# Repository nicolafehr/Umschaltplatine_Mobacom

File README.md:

# Umschaltplatine_Mobacom
PCB um die Steuerung einer Testanlage mit verschiedenen Zentralen zu ermöglichen. Zudem können verschiedene Gleisabschnitte angesteuert werden können.

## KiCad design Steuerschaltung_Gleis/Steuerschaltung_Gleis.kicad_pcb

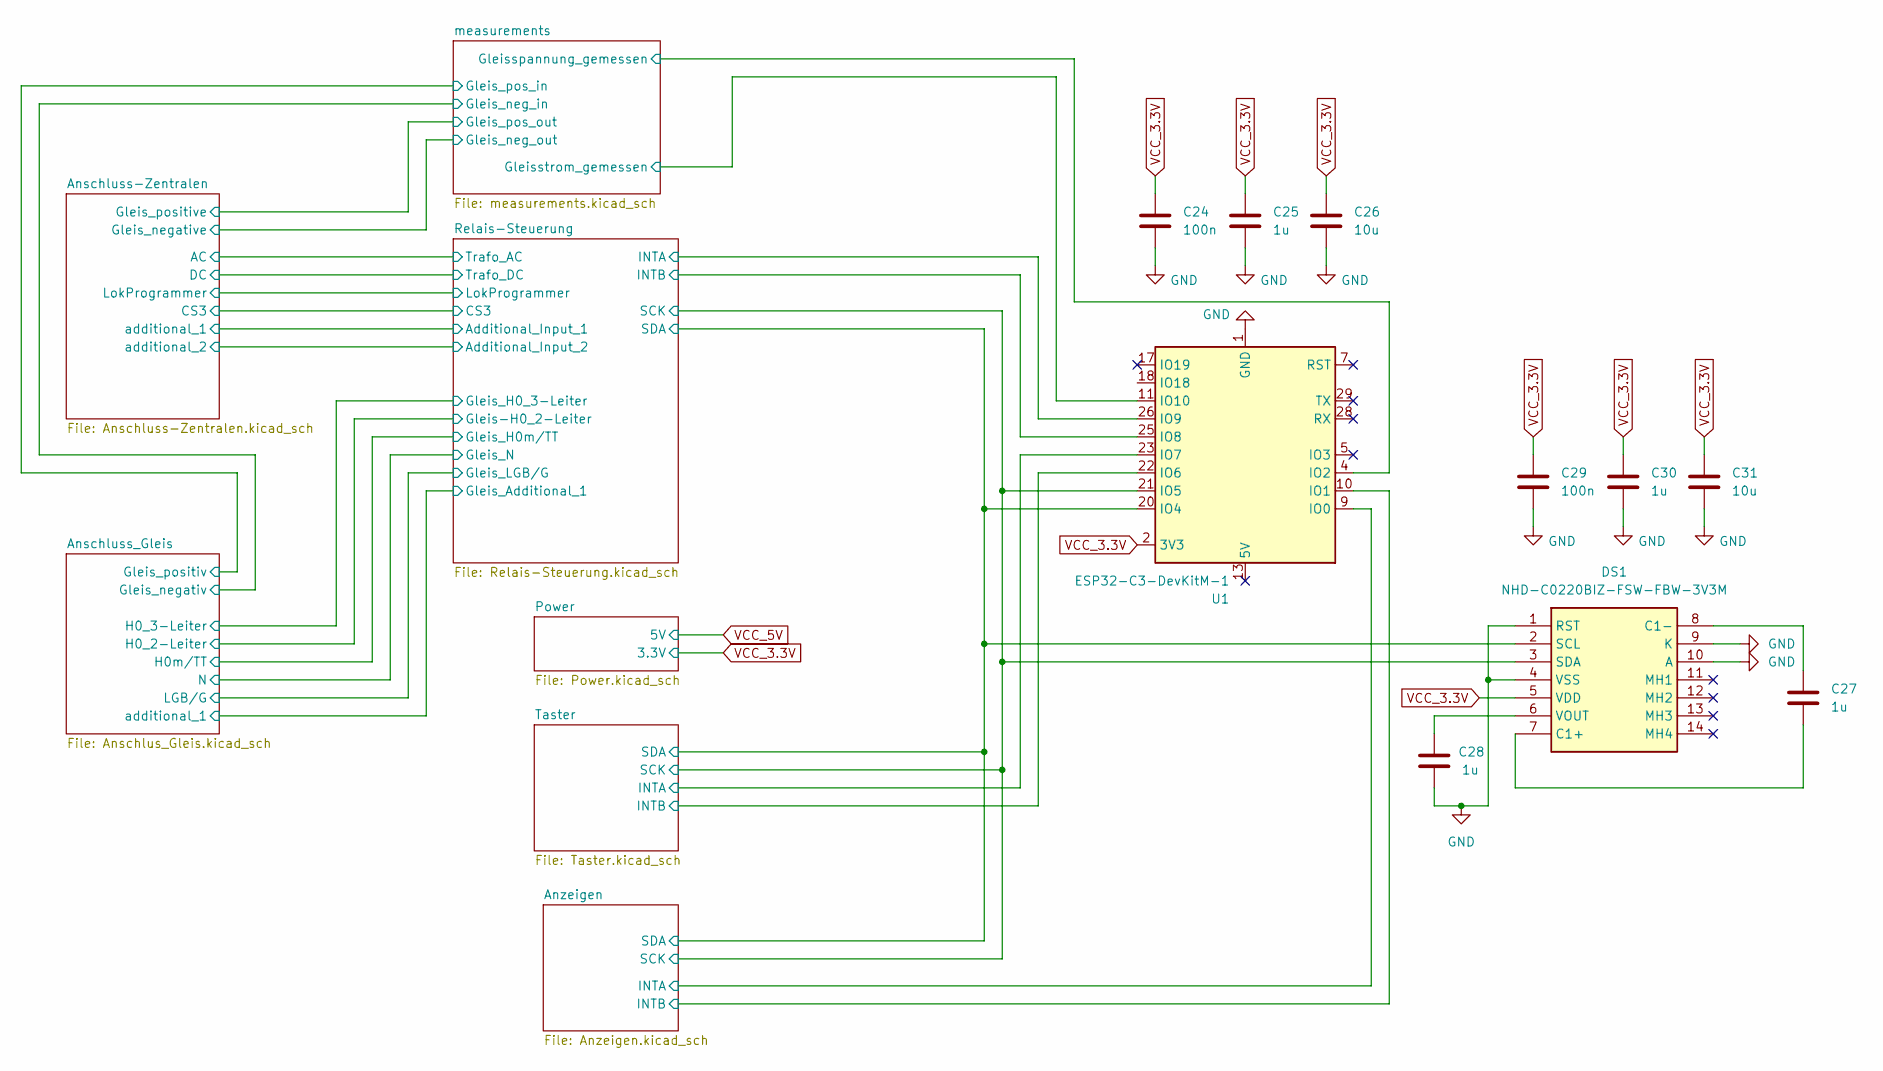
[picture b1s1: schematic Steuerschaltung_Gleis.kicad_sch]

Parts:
C24, C29: 100n; C_0805_2012Metric
C25, C27, C28, C30: 1u; C_0805_2012Metric
C26, C31: 10u; C_0805_2012Metric
DS1: NHD-C0220BIZ-FSW-FBW-3V3M; NHDC0220BIZFSWFBW3V3M; Mouser Part Number 763-C0220BIZ-FSW-FBW
U1: ESP32-C3-DevKitM-1

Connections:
/Anzeigen/INTA: U1.9 (IO0); also elsewhere on the board
/Anzeigen/INTB: U1.10 (IO1); also elsewhere on the board
/Anzeigen/SCK: DS1.3 (SDA), U1.21 (IO5); also elsewhere on the board
/Anzeigen/SDA: DS1.2 (SCL), U1.20 (IO4); also elsewhere on the board
/Relais-Steuerung/INTA: U1.26 (IO9); also elsewhere on the board
/Relais-Steuerung/INTB: U1.25 (IO8); also elsewhere on the board
/Taster/INTA: U1.23 (IO7); also elsewhere on the board
/Taster/INTB: U1.22 (IO6); also elsewhere on the board
/measurements/Gleisspannung_gemessen: U1.4 (IO2); also elsewhere on the board
/measurements/Gleisstrom_gemessen: U1.11 (IO10); also elsewhere on the board
GND: C24.2, C25.2, C26.2, C28.2, C29.2, C30.2, C31.2, DS1.1 (RST), DS1.4 (VSS), DS1.9 (K), DS1.10 (A), U1.1 (GND), U1.6 (GND), U1.8 (GND), U1.12 (GND), U1.15 (GND), U1.16 (GND), U1.19 (GND), U1.24 (GND), U1.27 (GND), U1.30 (GND); also elsewhere on the board
unnamed: C27.2, DS1.7 (C1+)
unnamed: C27.1, DS1.8 (C1-)
unnamed: C28.1, DS1.6 (VOUT)
VCC_3.3V: C24.1, C25.1, C26.1, C29.1, C30.1, C31.1, DS1.5 (VDD), U1.2 (3V3), U1.3 (3V3); also elsewhere on the board

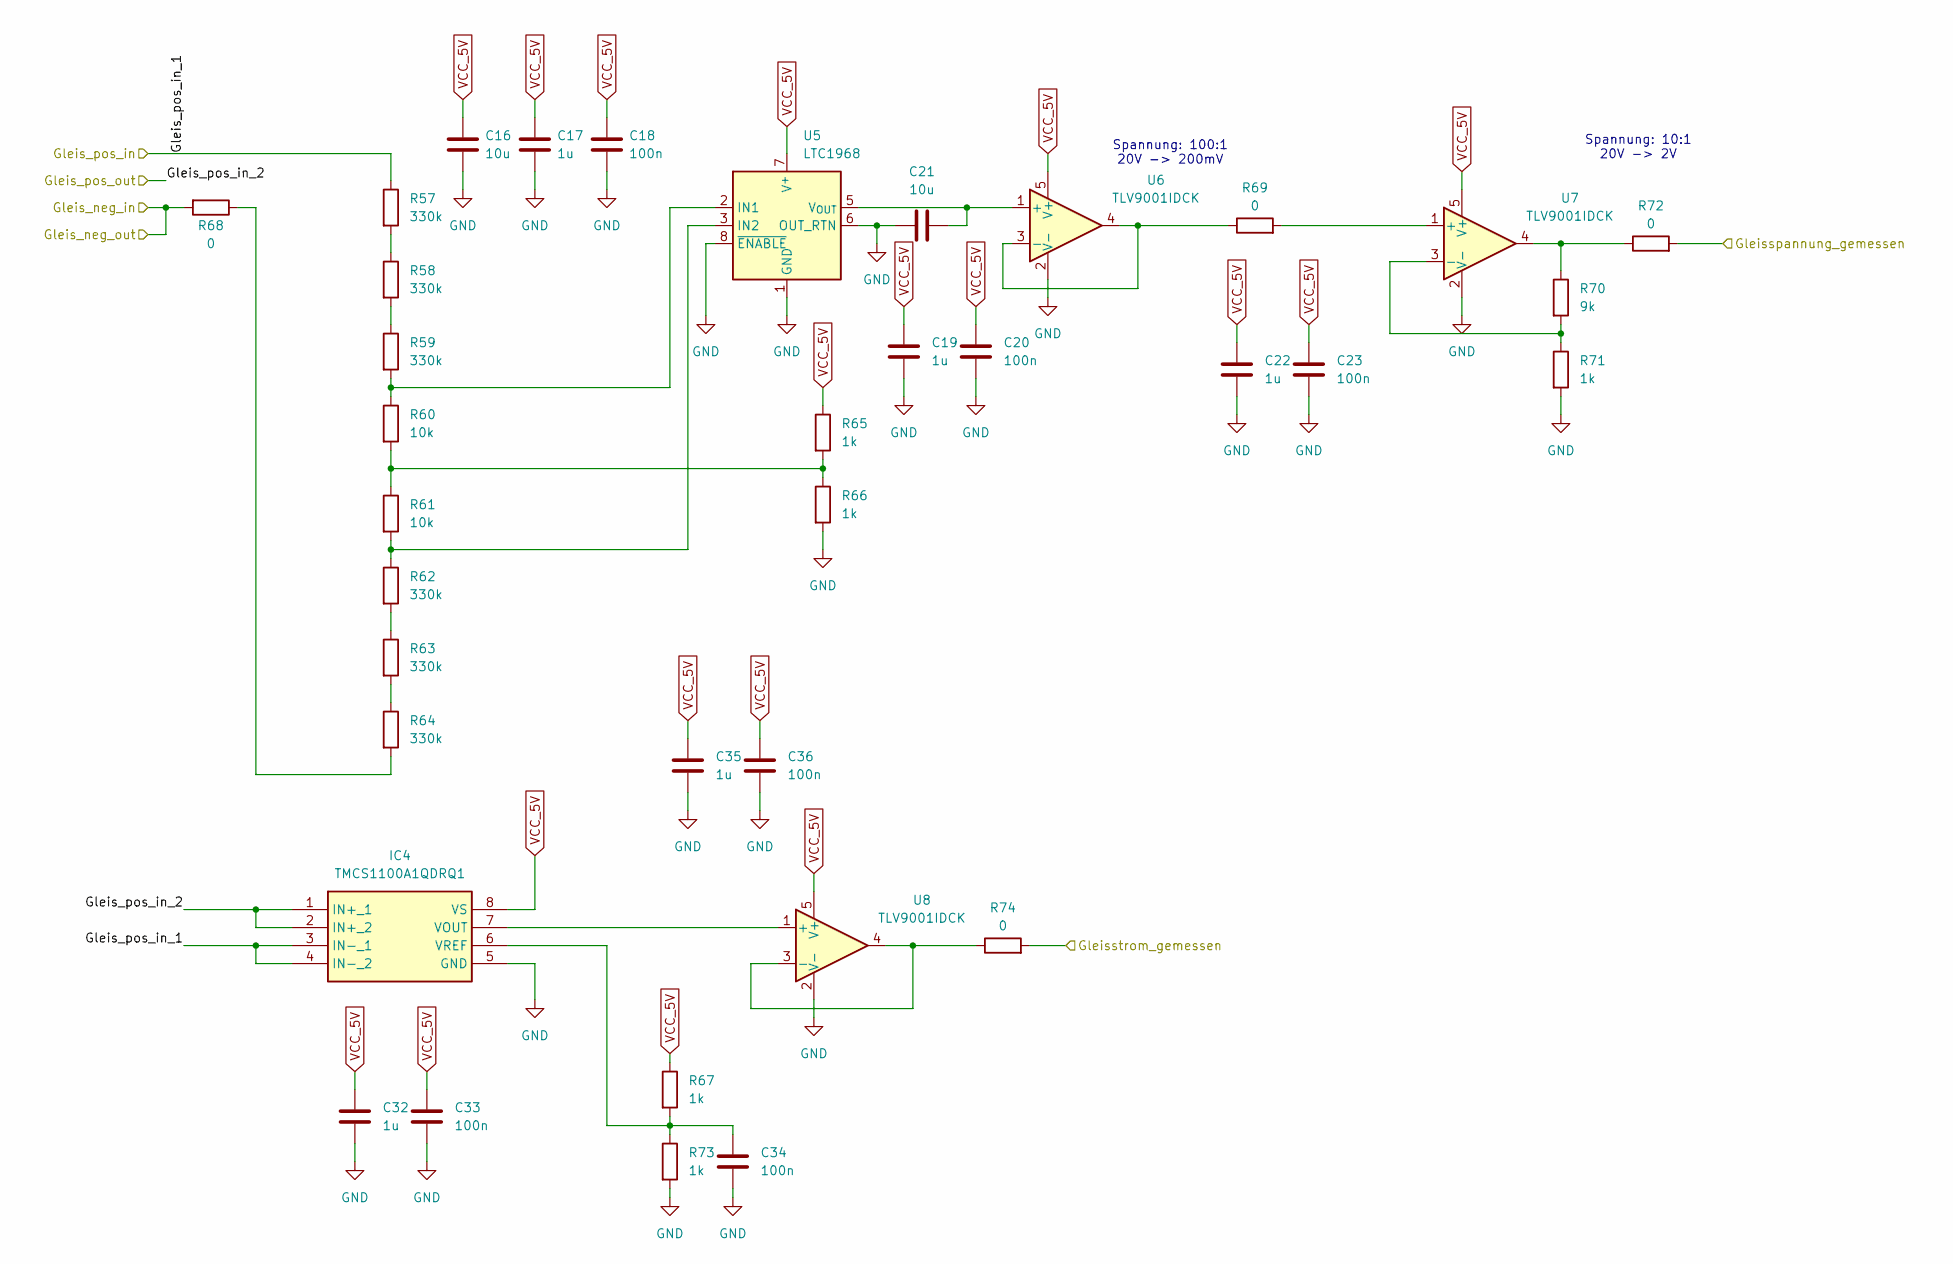
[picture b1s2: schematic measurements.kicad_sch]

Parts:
C16, C21: 10u; C_0805_2012Metric
C17, C19, C22, C32, C35: 1u; C_0805_2012Metric
C18, C20, C23, C33, C34, C36: 100n; C_0805_2012Metric
IC4: TMCS1100A1QDRQ1; SOIC127P600X175-8N; Mouser Part Number 595-TMCS1100A1QDRQ1
R57, R58, R59, R62, R63, R64: 330k; R_0805_2012Metric
R60, R61: 10k; R_0805_2012Metric
R65, R66, R67, R71, R73: 1k; R_0805_2012Metric
R68, R69, R72, R74: 0; R_0805_2012Metric
R70: 9k; R_0805_2012Metric
U5: LTC1968; MSOP-8_3x3mm_P0.65mm
U6, U7, U8: TLV9001IDCK; SOT-353_SC-70-5

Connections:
/Anschluss-Zentralen/Gleis_negative: R68.2; also elsewhere on the board
/measurements/Gleis_pos_in_1: IC4.3 (IN-_1), IC4.4 (IN-_2), R57.1; also elsewhere on the board
/measurements/Gleis_pos_in_2: IC4.1 (IN+_1), IC4.2 (IN+_2); also elsewhere on the board
/measurements/Gleisspannung_gemessen: R72.2; also elsewhere on the board
/measurements/Gleisstrom_gemessen: R74.2; also elsewhere on the board
GND: C16.2, C17.2, C18.2, C19.2, C20.2, C21.1, C22.2, C23.2, C32.2, C33.2, C34.2, C35.2, C36.2, IC4.5 (GND), R66.2, R71.2, R73.2, U5.1 (GND), U5.6 (OUT_RTN), U5.8 (~ENABLE), U6.2 (V-), U7.2 (V-), U8.2 (V-); also elsewhere on the board
unnamed: IC4.7 (VOUT), U8.1 (+)
unnamed: C34.1, IC4.6 (VREF), R67.2, R73.1
unnamed: R57.2, R58.1
unnamed: R58.2, R59.1
unnamed: R60.2, R61.1, R65.2, R66.1
unnamed: R62.2, R63.1
unnamed: R63.2, R64.1
unnamed: R64.2, R68.1
unnamed: R70.1, R72.1, U7.4
unnamed: R59.2, R60.1, U5.2 (IN1)
unnamed: R61.2, R62.1, U5.3 (IN2)
unnamed: C21.2, U5.5 (V_{OUT}), U6.1 (+)
unnamed: R69.1, U6.3 (-), U6.4
unnamed: R69.2, U7.1 (+)
unnamed: R70.2, R71.1, U7.3 (-)
unnamed: R74.1, U8.3 (-), U8.4
VCC_5V: C16.1, C17.1, C18.1, C19.1, C20.1, C22.1, C23.1, C32.1, C33.1, C35.1, C36.1, IC4.8 (VS), R65.1, R67.1, U5.7 (V^{+}), U6.5 (V+), U7.5 (V+), U8.5 (V+); also elsewhere on the board

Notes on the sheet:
Spannung: 100:1 20V -> 200mV
Spannung: 10:1 20V -> 2V

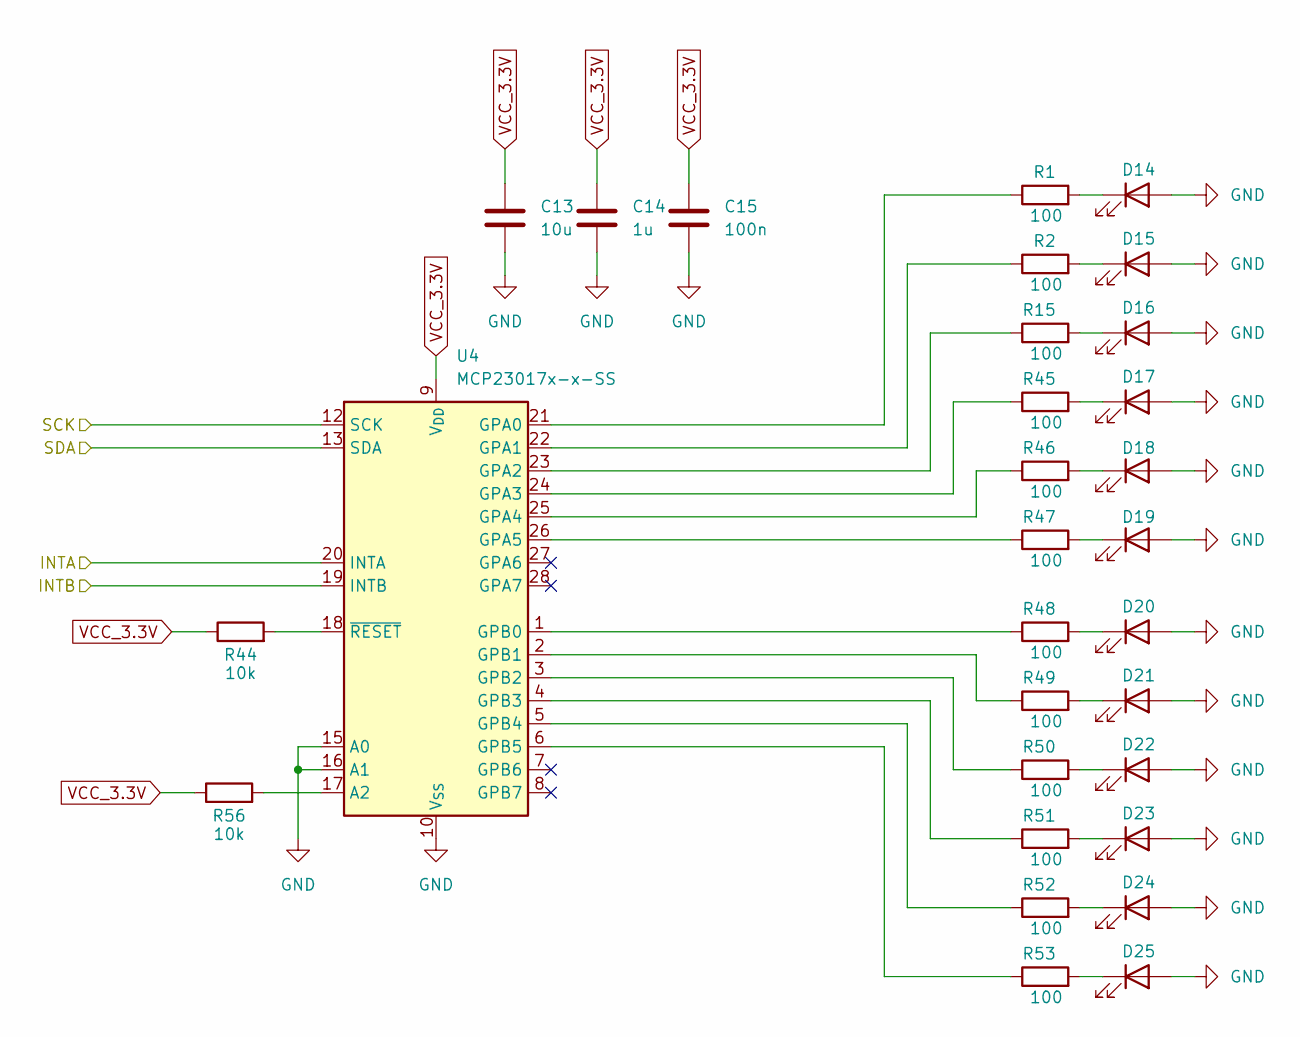
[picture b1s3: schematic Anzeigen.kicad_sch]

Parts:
C13: 10u; C_0805_2012Metric
C14: 1u; C_0805_2012Metric
C15: 100n; C_0805_2012Metric
D14, D15, D16, D17, D18, D19, D20, D21, D22, D23, D24, D25: LED; LED_D3.0mm
R1, R2, R15, R45, R46, R47, R48, R49, R50, R51, R52, R53: 100; R_0805_2012Metric
R44, R56: 10k; R_0805_2012Metric
U4: MCP23017x-x-SS; SSOP-28_5.3x10.2mm_P0.65mm

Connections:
/Anzeigen/INTA: U4.20 (INTA); also elsewhere on the board
/Anzeigen/INTB: U4.19 (INTB); also elsewhere on the board
/Anzeigen/SCK: U4.12 (SCK); also elsewhere on the board
/Anzeigen/SDA: U4.13 (SDA); also elsewhere on the board
GND: C13.2, C14.2, C15.2, D14.2 (A), D15.2 (A), D16.2 (A), D17.2 (A), D18.2 (A), D19.2 (A), D20.2 (A), D21.2 (A), D22.2 (A), D23.2 (A), D24.2 (A), D25.2 (A), U4.10 (V_{SS}), U4.15 (A0), U4.16 (A1); also elsewhere on the board
unnamed: D14.1 (K), R1.2
unnamed: D15.1 (K), R2.2
unnamed: D16.1 (K), R15.2
unnamed: D17.1 (K), R45.2
unnamed: D18.1 (K), R46.2
unnamed: D19.1 (K), R47.2
unnamed: D20.1 (K), R48.2
unnamed: D21.1 (K), R49.2
unnamed: D22.1 (K), R50.2
unnamed: D23.1 (K), R51.2
unnamed: D24.1 (K), R52.2
unnamed: D25.1 (K), R53.2
unnamed: R56.2, U4.17 (A2)
unnamed: R1.1, U4.21 (GPA0)
unnamed: R2.1, U4.22 (GPA1)
unnamed: R15.1, U4.23 (GPA2)
unnamed: R45.1, U4.24 (GPA3)
unnamed: R46.1, U4.25 (GPA4)
unnamed: R47.1, U4.26 (GPA5)
unnamed: R48.1, U4.1 (GPB0)
unnamed: R49.1, U4.2 (GPB1)
unnamed: R50.1, U4.3 (GPB2)
unnamed: R51.1, U4.4 (GPB3)
unnamed: R52.1, U4.5 (GPB4)
unnamed: R53.1, U4.6 (GPB5)
unnamed: R44.2, U4.18 (~RESET)
VCC_3.3V: C13.1, C14.1, C15.1, R44.1, R56.1, U4.9 (V_{DD}); also elsewhere on the board

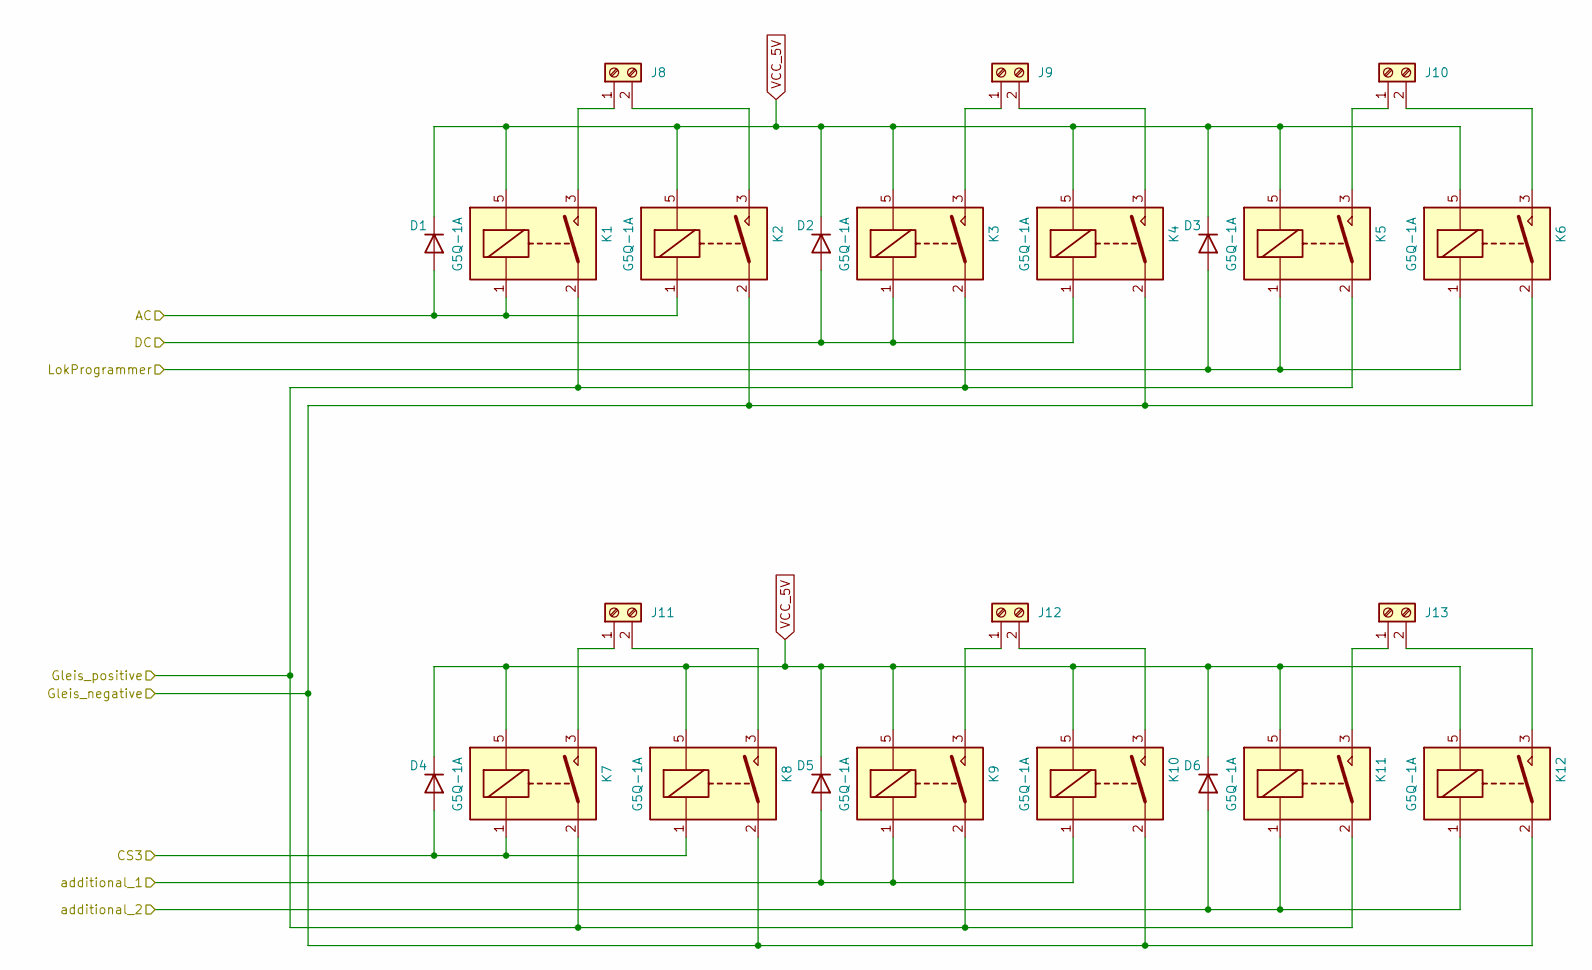
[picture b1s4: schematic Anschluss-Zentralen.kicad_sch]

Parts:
D1, D2, D3, D4, D5, D6: 1N4148; D_DO-35_SOD27_P7.62mm_Horizontal
J8, J9, J10, J11, J12, J13: Screw_Terminal_01x02; TerminalBlock_Phoenix_MKDS-1,5-2_1x02_P5.00mm_Horizontal
K1, K2, K3, K4, K5, K6, K7, K8, K9, K10, K11, K12: G5Q-1A; Relay_SPST_Omron-G5Q-1A

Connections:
/Anschluss-Zentralen/AC: D1.2 (A), K1.1, K2.1; also elsewhere on the board
/Anschluss-Zentralen/CS3: D4.2 (A), K7.1, K8.1; also elsewhere on the board
/Anschluss-Zentralen/DC: D2.2 (A), K3.1, K4.1; also elsewhere on the board
/Anschluss-Zentralen/Gleis_negative: K2.2, K4.2, K6.2, K8.2, K10.2, K12.2; also elsewhere on the board
/Anschluss-Zentralen/LokProgrammer: D3.2 (A), K5.1, K6.1; also elsewhere on the board
/Anschluss-Zentralen/additional_1: D5.2 (A), K9.1, K10.1; also elsewhere on the board
/Anschluss-Zentralen/additional_2: D6.2 (A), K11.1, K12.1; also elsewhere on the board
/measurements/Gleis_pos_in_2: K1.2, K3.2, K5.2, K7.2, K9.2, K11.2; also elsewhere on the board
unnamed: J8.1, K1.3
unnamed: J8.2, K2.3
unnamed: J9.1, K3.3
unnamed: J9.2, K4.3
unnamed: J10.1, K5.3
unnamed: J10.2, K6.3
unnamed: J11.1, K7.3
unnamed: J11.2, K8.3
unnamed: J12.1, K9.3
unnamed: J12.2, K10.3
unnamed: J13.1, K11.3
unnamed: J13.2, K12.3
VCC_5V: D1.1 (K), D2.1 (K), D3.1 (K), D4.1 (K), D5.1 (K), D6.1 (K), K1.5, K2.5, K3.5, K4.5, K5.5, K6.5, K7.5, K8.5, K9.5, K10.5, K11.5, K12.5; also elsewhere on the board

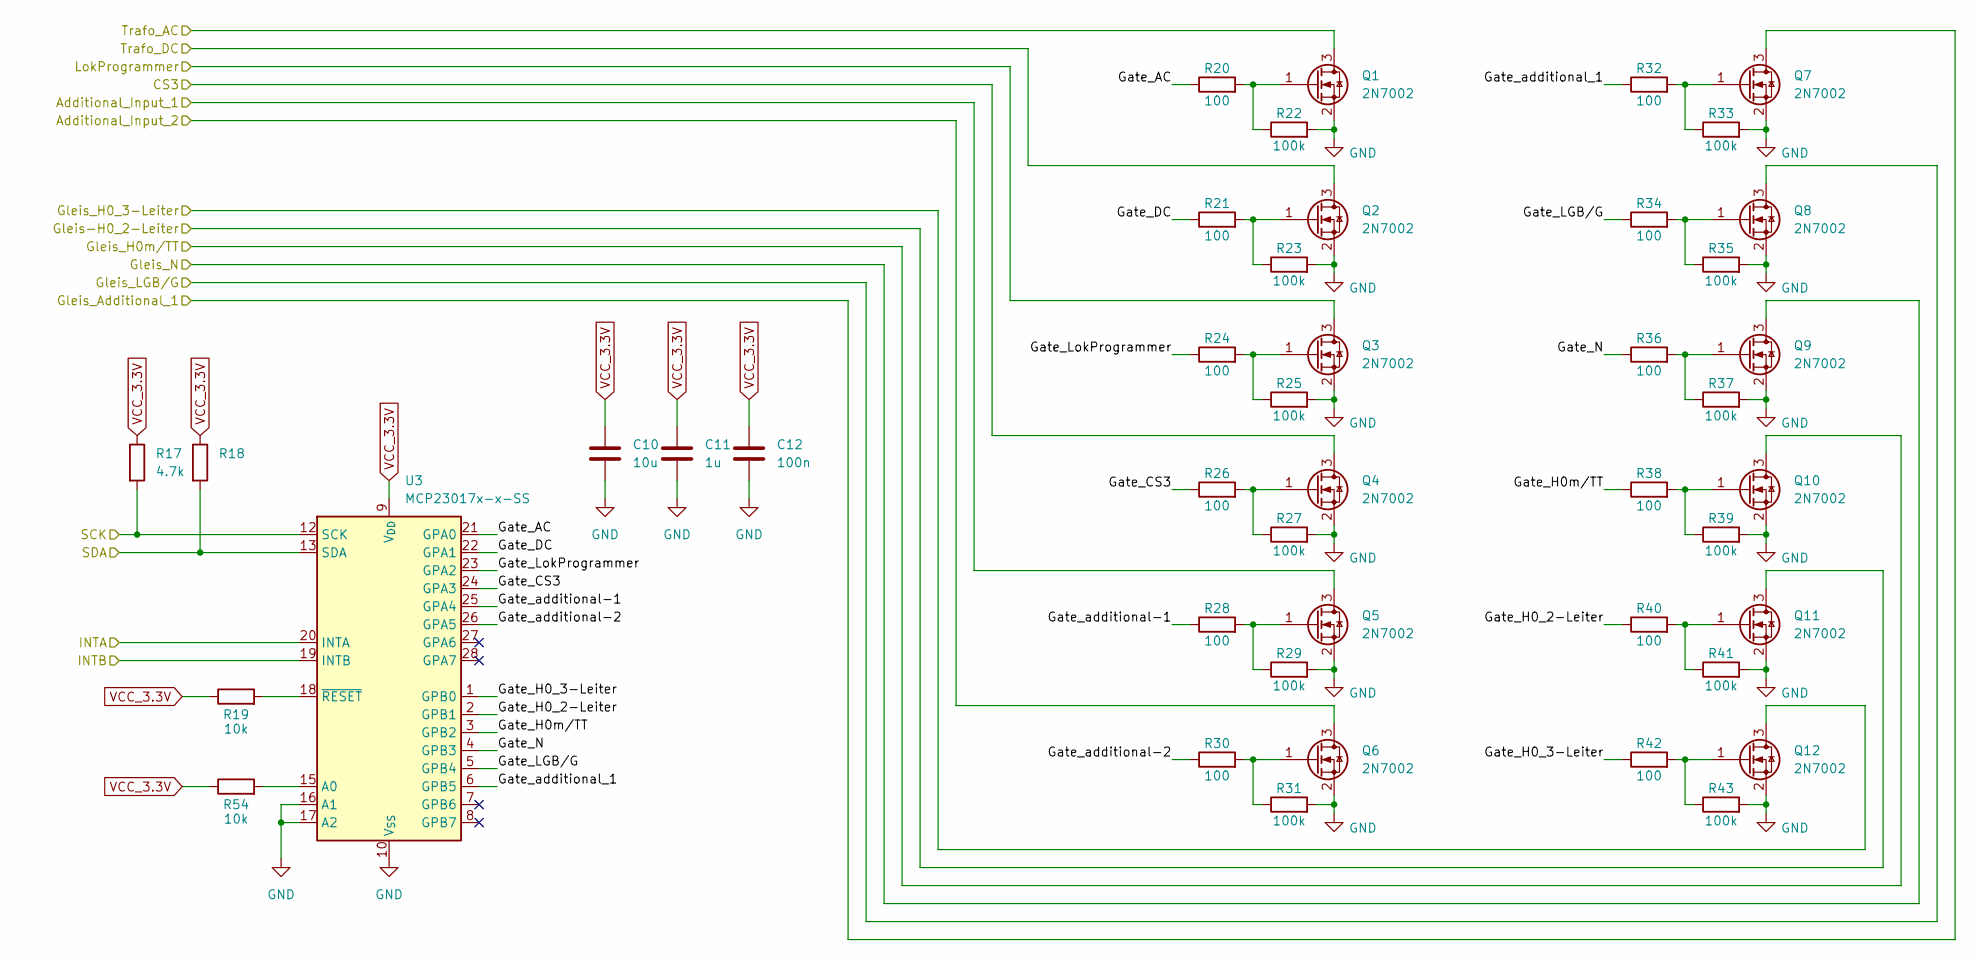
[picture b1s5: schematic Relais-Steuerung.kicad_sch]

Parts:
C10: 10u; C_0805_2012Metric
C11: 1u; C_0805_2012Metric
C12: 100n; C_0805_2012Metric
Q1, Q2, Q3, Q4, Q5, Q6, Q7, Q8, Q9, Q10, Q11, Q12: 2N7002; SOT-23
R17, R18: 4.7k; R_0805_2012Metric
R19, R54: 10k; R_0805_2012Metric
R20, R21, R24, R26, R28, R30, R32, R34, R36, R38, R40, R42: 100; R_0805_2012Metric
R22, R23, R25, R27, R29, R31, R33, R35, R37, R39, R41, R43: 100k; R_0805_2012Metric
U3: MCP23017x-x-SS; SSOP-28_5.3x10.2mm_P0.65mm

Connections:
/Anschluss-Zentralen/AC: Q1.3 (D); also elsewhere on the board
/Anschluss-Zentralen/CS3: Q4.3 (D); also elsewhere on the board
/Anschluss-Zentralen/DC: Q2.3 (D); also elsewhere on the board
/Anschluss-Zentralen/LokProgrammer: Q3.3 (D); also elsewhere on the board
/Anschluss-Zentralen/additional_1: Q5.3 (D); also elsewhere on the board
/Anschluss-Zentralen/additional_2: Q6.3 (D); also elsewhere on the board
/Anschluss_Gleis/H0_2-Leiter: Q11.3 (D); also elsewhere on the board
/Anschluss_Gleis/H0_3-Leiter: Q12.3 (D); also elsewhere on the board
/Anschluss_Gleis/H0m/TT: Q10.3 (D); also elsewhere on the board
/Anschluss_Gleis/LGB/G: Q8.3 (D); also elsewhere on the board
/Anschluss_Gleis/N: Q9.3 (D); also elsewhere on the board
/Anschluss_Gleis/additional_1: Q7.3 (D); also elsewhere on the board
/Anzeigen/SCK: R17.2, U3.12 (SCK); also elsewhere on the board
/Anzeigen/SDA: R18.2, U3.13 (SDA); also elsewhere on the board
/Relais-Steuerung/Gate_AC: R20.1, U3.21 (GPA0)
/Relais-Steuerung/Gate_CS3: R26.1, U3.24 (GPA3)
/Relais-Steuerung/Gate_DC: R21.1, U3.22 (GPA1)
/Relais-Steuerung/Gate_H0_2-Leiter: R40.1, U3.2 (GPB1)
/Relais-Steuerung/Gate_H0_3-Leiter: R42.1, U3.1 (GPB0)
/Relais-Steuerung/Gate_H0m/TT: R38.1, U3.3 (GPB2)
/Relais-Steuerung/Gate_LGB/G: R34.1, U3.5 (GPB4)
/Relais-Steuerung/Gate_LokProgrammer: R24.1, U3.23 (GPA2)
/Relais-Steuerung/Gate_N: R36.1, U3.4 (GPB3)
/Relais-Steuerung/Gate_additional-1: R28.1, U3.25 (GPA4)
/Relais-Steuerung/Gate_additional-2: R30.1, U3.26 (GPA5)
/Relais-Steuerung/Gate_additional_1: R32.1, U3.6 (GPB5)
/Relais-Steuerung/INTA: U3.20 (INTA); also elsewhere on the board
/Relais-Steuerung/INTB: U3.19 (INTB); also elsewhere on the board
GND: C10.2, C11.2, C12.2, Q1.2 (S), Q2.2 (S), Q3.2 (S), Q4.2 (S), Q5.2 (S), Q6.2 (S), Q7.2 (S), Q8.2 (S), Q9.2 (S), Q10.2 (S), Q11.2 (S), Q12.2 (S), R22.2, R23.2, R25.2, R27.2, R29.2, R31.2, R33.2, R35.2, R37.2, R39.2, R41.2, R43.2, U3.10 (V_{SS}), U3.16 (A1), U3.17 (A2); also elsewhere on the board
unnamed: Q1.1 (G), R20.2, R22.1
unnamed: Q2.1 (G), R21.2, R23.1
unnamed: Q3.1 (G), R24.2, R25.1
unnamed: Q4.1 (G), R26.2, R27.1
unnamed: Q5.1 (G), R28.2, R29.1
unnamed: Q6.1 (G), R30.2, R31.1
unnamed: Q7.1 (G), R32.2, R33.1
unnamed: Q8.1 (G), R34.2, R35.1
unnamed: Q9.1 (G), R36.2, R37.1
unnamed: Q10.1 (G), R38.2, R39.1
unnamed: Q11.1 (G), R40.2, R41.1
unnamed: Q12.1 (G), R42.2, R43.1
unnamed: R54.2, U3.15 (A0)
unnamed: R19.2, U3.18 (~RESET)
VCC_3.3V: C10.1, C11.1, C12.1, R17.1, R18.1, R19.1, R54.1, U3.9 (V_{DD}); also elsewhere on the board

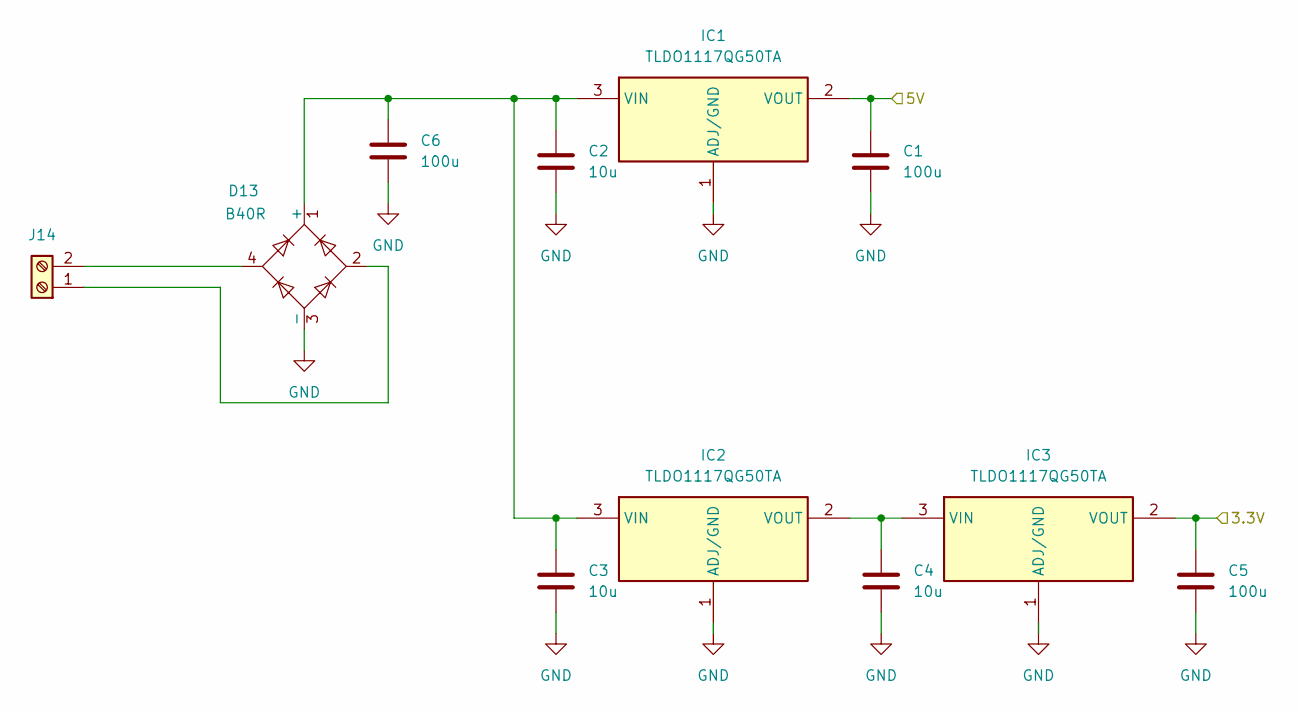
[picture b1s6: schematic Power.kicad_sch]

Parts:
C1, C5, C6: 100u; C_1206_3216Metric
C2, C3, C4: 10u; C_0805_2012Metric
D13: B40R; Diode_Bridge_Round_D9.0mm
IC1, IC2, IC3: TLDO1117QG50TA; SOT-223; Mouser Part Number 621-ZLDO1117QG12TA
J14: Screw_Terminal_01x02; TerminalBlock_Phoenix_MKDS-1,5-2_1x02_P5.00mm_Horizontal

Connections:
GND: C1.2, C2.2, C3.2, C4.2, C5.2, C6.2, D13.3 (-), IC1.1 (ADJ/GND), IC2.1 (ADJ/GND), IC3.1 (ADJ/GND); also elsewhere on the board
unnamed: C2.1, C3.1, C6.1, D13.1 (+), IC1.3 (VIN), IC2.3 (VIN)
unnamed: C4.1, IC2.2 (VOUT), IC3.3 (VIN)
unnamed: D13.2, J14.1
unnamed: D13.4, J14.2
VCC_3.3V: C5.1, IC3.2 (VOUT); also elsewhere on the board
VCC_5V: C1.1, IC1.2 (VOUT); also elsewhere on the board

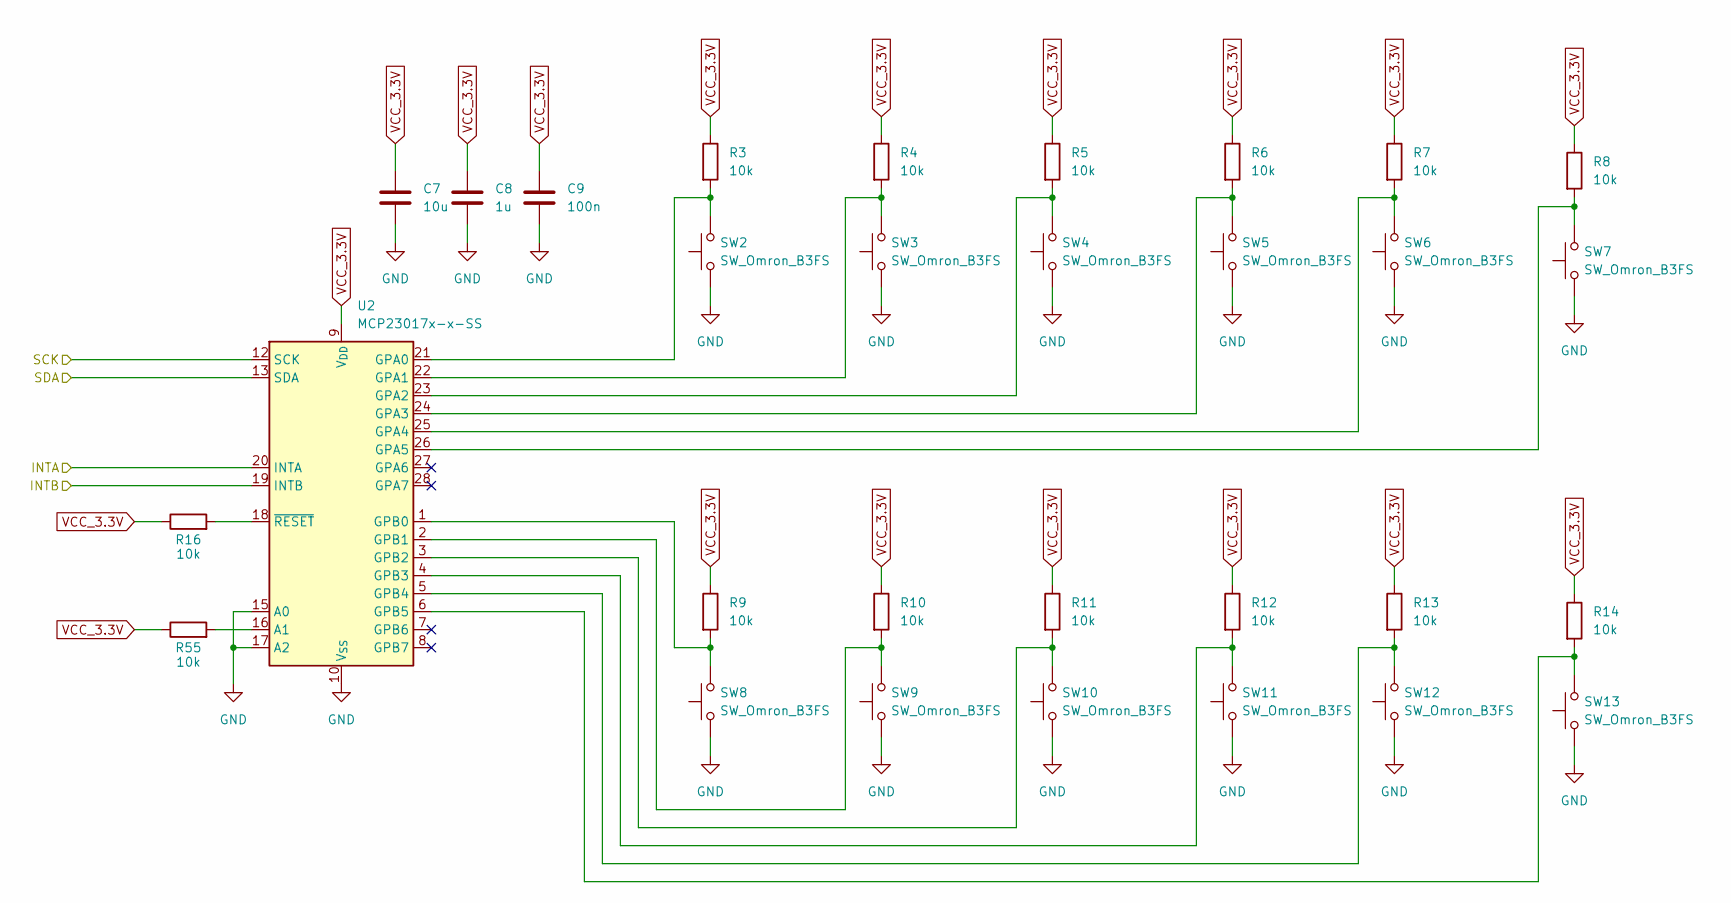
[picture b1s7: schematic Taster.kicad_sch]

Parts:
C7: 10u; C_0805_2012Metric
C8: 1u; C_0805_2012Metric
C9: 100n; C_0805_2012Metric
R3, R4, R5, R6, R7, R8, R9, R10, R11, R12, R13, R14, R16, R55: 10k; R_0805_2012Metric
SW2, SW3, SW4, SW5, SW6, SW7, SW8, SW9, SW10, SW11, SW12, SW13: SW_Omron_B3FS; SW_TH_Tactile_Omron_B3F-100x
U2: MCP23017x-x-SS; SSOP-28_5.3x10.2mm_P0.65mm

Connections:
/Anzeigen/SCK: U2.12 (SCK); also elsewhere on the board
/Anzeigen/SDA: U2.13 (SDA); also elsewhere on the board
/Taster/INTA: U2.20 (INTA); also elsewhere on the board
/Taster/INTB: U2.19 (INTB); also elsewhere on the board
GND: C7.2, C8.2, C9.2, SW2.1, SW3.1, SW4.1, SW5.1, SW6.1, SW7.1, SW8.1, SW9.1, SW10.1, SW11.1, SW12.1, SW13.1, U2.10 (V_{SS}), U2.15 (A0), U2.17 (A2); also elsewhere on the board
unnamed: R55.2, U2.16 (A1)
unnamed: R3.2, SW2.2, U2.21 (GPA0)
unnamed: R4.2, SW3.2, U2.22 (GPA1)
unnamed: R5.2, SW4.2, U2.23 (GPA2)
unnamed: R6.2, SW5.2, U2.24 (GPA3)
unnamed: R7.2, SW6.2, U2.25 (GPA4)
unnamed: R8.2, SW7.2, U2.26 (GPA5)
unnamed: R9.2, SW8.2, U2.1 (GPB0)
unnamed: R10.2, SW9.2, U2.2 (GPB1)
unnamed: R11.2, SW10.2, U2.3 (GPB2)
unnamed: R12.2, SW11.2, U2.4 (GPB3)
unnamed: R13.2, SW12.2, U2.5 (GPB4)
unnamed: R14.2, SW13.2, U2.6 (GPB5)
unnamed: R16.2, U2.18 (~RESET)
VCC_3.3V: C7.1, C8.1, C9.1, R3.1, R4.1, R5.1, R6.1, R7.1, R8.1, R9.1, R10.1, R11.1, R12.1, R13.1, R14.1, R16.1, R55.1, U2.9 (V_{DD}); also elsewhere on the board

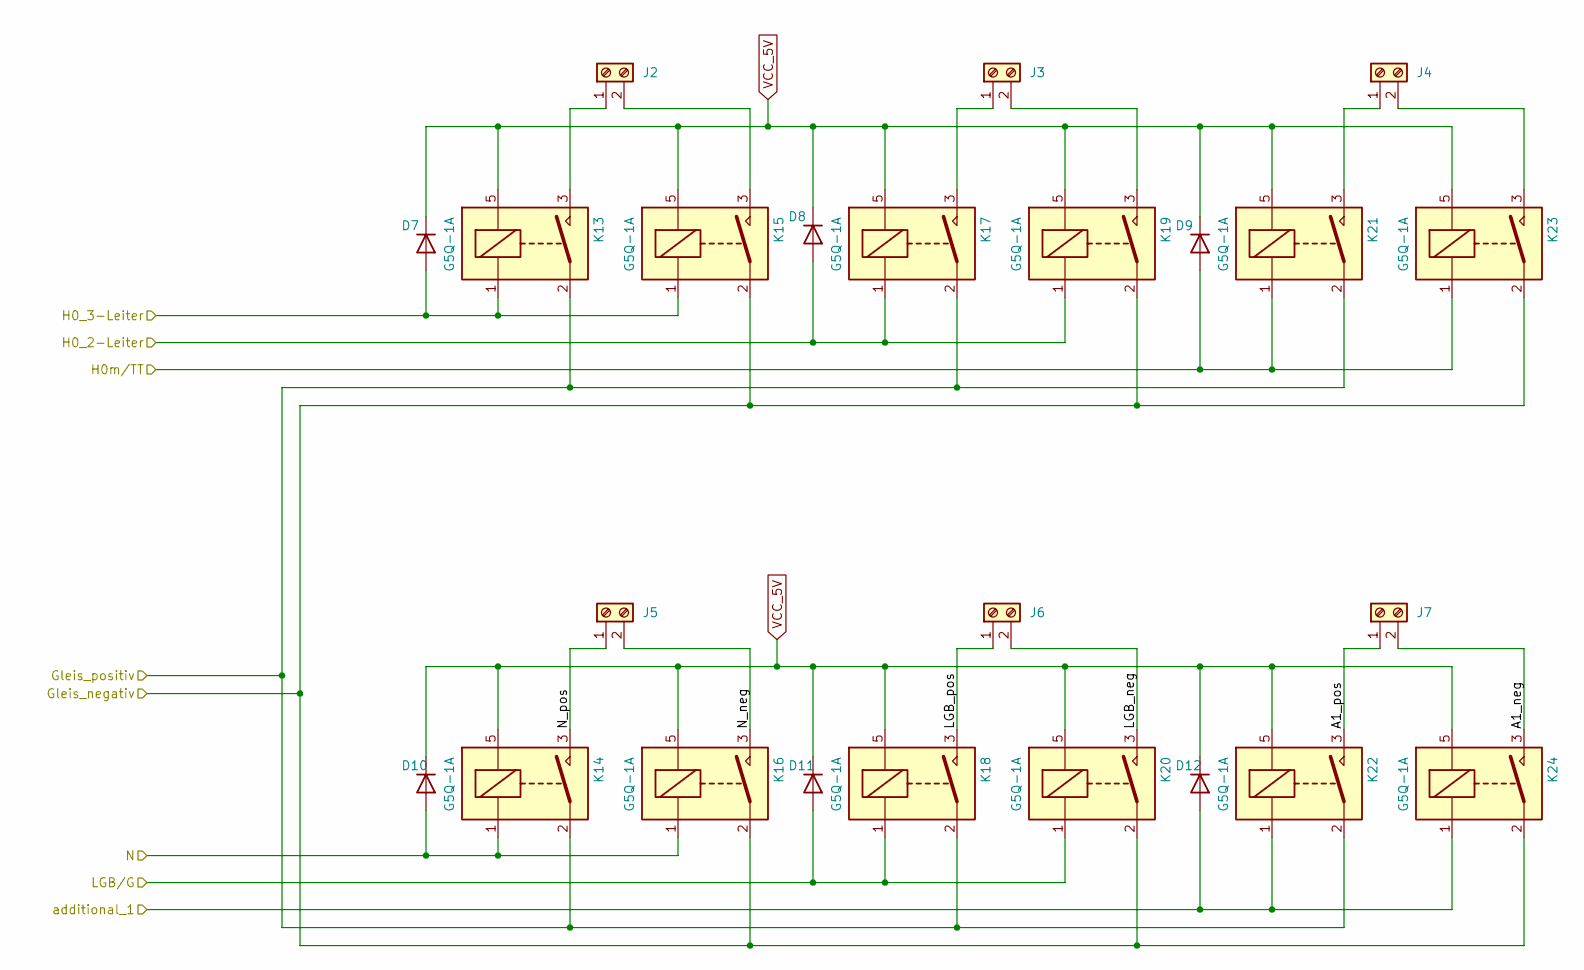
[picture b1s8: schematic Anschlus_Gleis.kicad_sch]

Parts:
D7, D8, D9, D10, D11, D12: 1N4148; D_DO-35_SOD27_P7.62mm_Horizontal
J2, J3, J4, J5, J6, J7: Screw_Terminal_01x02; TerminalBlock_Phoenix_MKDS-1,5-2_1x02_P5.00mm_Horizontal
K13, K14, K15, K16, K17, K18, K19, K20, K21, K22, K23, K24: G5Q-1A; Relay_SPST_Omron-G5Q-1A

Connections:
/Anschluss-Zentralen/Gleis_negative: K15.2, K16.2, K19.2, K20.2, K23.2, K24.2; also elsewhere on the board
/Anschluss_Gleis/A1_neg: J7.2, K24.3
/Anschluss_Gleis/A1_pos: J7.1, K22.3
/Anschluss_Gleis/H0_2-Leiter: D8.2 (A), K17.1, K19.1; also elsewhere on the board
/Anschluss_Gleis/H0_3-Leiter: D7.2 (A), K13.1, K15.1; also elsewhere on the board
/Anschluss_Gleis/H0m/TT: D9.2 (A), K21.1, K23.1; also elsewhere on the board
/Anschluss_Gleis/LGB_neg: J6.2, K20.3
/Anschluss_Gleis/LGB_pos: J6.1, K18.3
/Anschluss_Gleis/LGB/G: D11.2 (A), K18.1, K20.1; also elsewhere on the board
/Anschluss_Gleis/N: D10.2 (A), K14.1, K16.1; also elsewhere on the board
/Anschluss_Gleis/N_neg: J5.2, K16.3
/Anschluss_Gleis/N_pos: J5.1, K14.3
/Anschluss_Gleis/additional_1: D12.2 (A), K22.1, K24.1; also elsewhere on the board
/measurements/Gleis_pos_in_1: K13.2, K14.2, K17.2, K18.2, K21.2, K22.2; also elsewhere on the board
unnamed: J2.1, K13.3
unnamed: J2.2, K15.3
unnamed: J3.1, K17.3
unnamed: J3.2, K19.3
unnamed: J4.1, K21.3
unnamed: J4.2, K23.3
VCC_5V: D7.1 (K), D8.1 (K), D9.1 (K), D10.1 (K), D11.1 (K), D12.1 (K), K13.5, K14.5, K15.5, K16.5, K17.5, K18.5, K19.5, K20.5, K21.5, K22.5, K23.5, K24.5; also elsewhere on the board

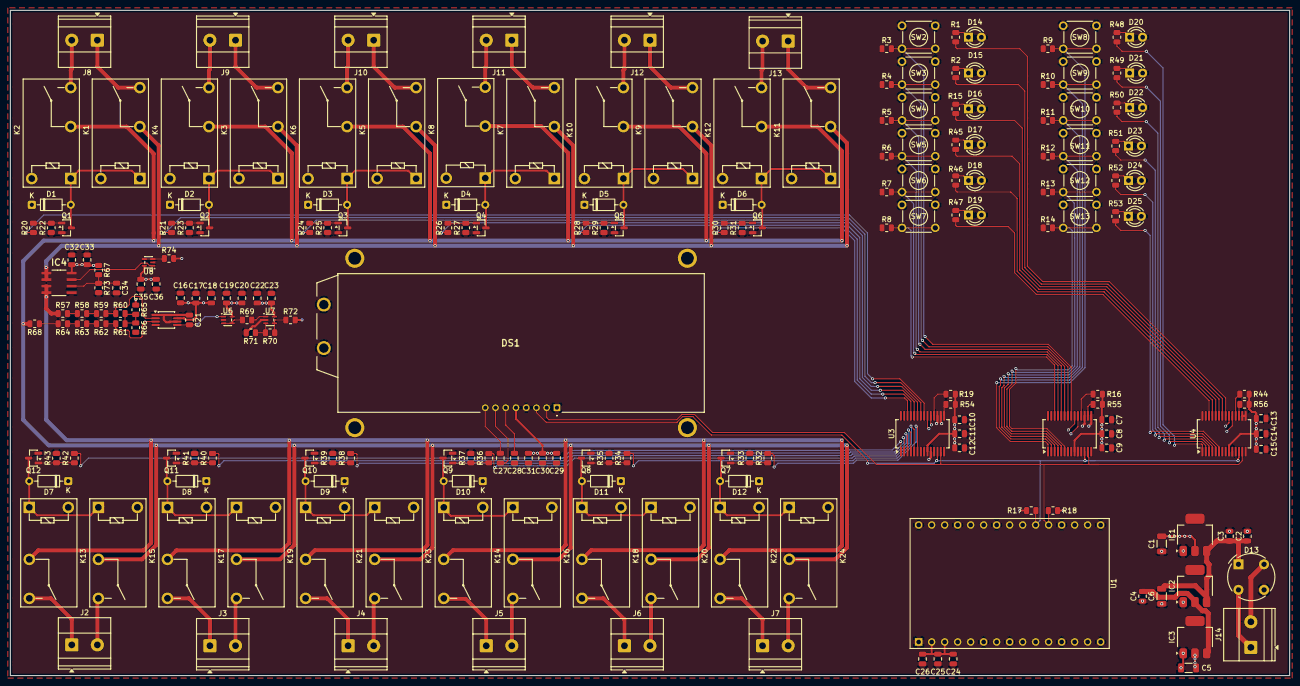
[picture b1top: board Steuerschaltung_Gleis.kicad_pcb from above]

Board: 4 copper layers, 250.0 x 130.0 mm, 209 parts (0 on the bottom side), 141 nets.
